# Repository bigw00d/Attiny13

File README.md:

# Attiny13 

This project is software and hardware resources to support my hobby. 

## Licence

   Licensed under the Apache License, Version 2.0 (the "License");
   you may not use this file except in compliance with the License.
   You may obtain a copy of the License at

       http://www.apache.org/licenses/LICENSE-2.0

   Unless required by applicable law or agreed to in writing, software
   distributed under the License is distributed on an "AS IS" BASIS,
   WITHOUT WARRANTIES OR CONDITIONS OF ANY KIND, either express or implied.
   See the License for the specific language governing permissions and
   limitations under the License.

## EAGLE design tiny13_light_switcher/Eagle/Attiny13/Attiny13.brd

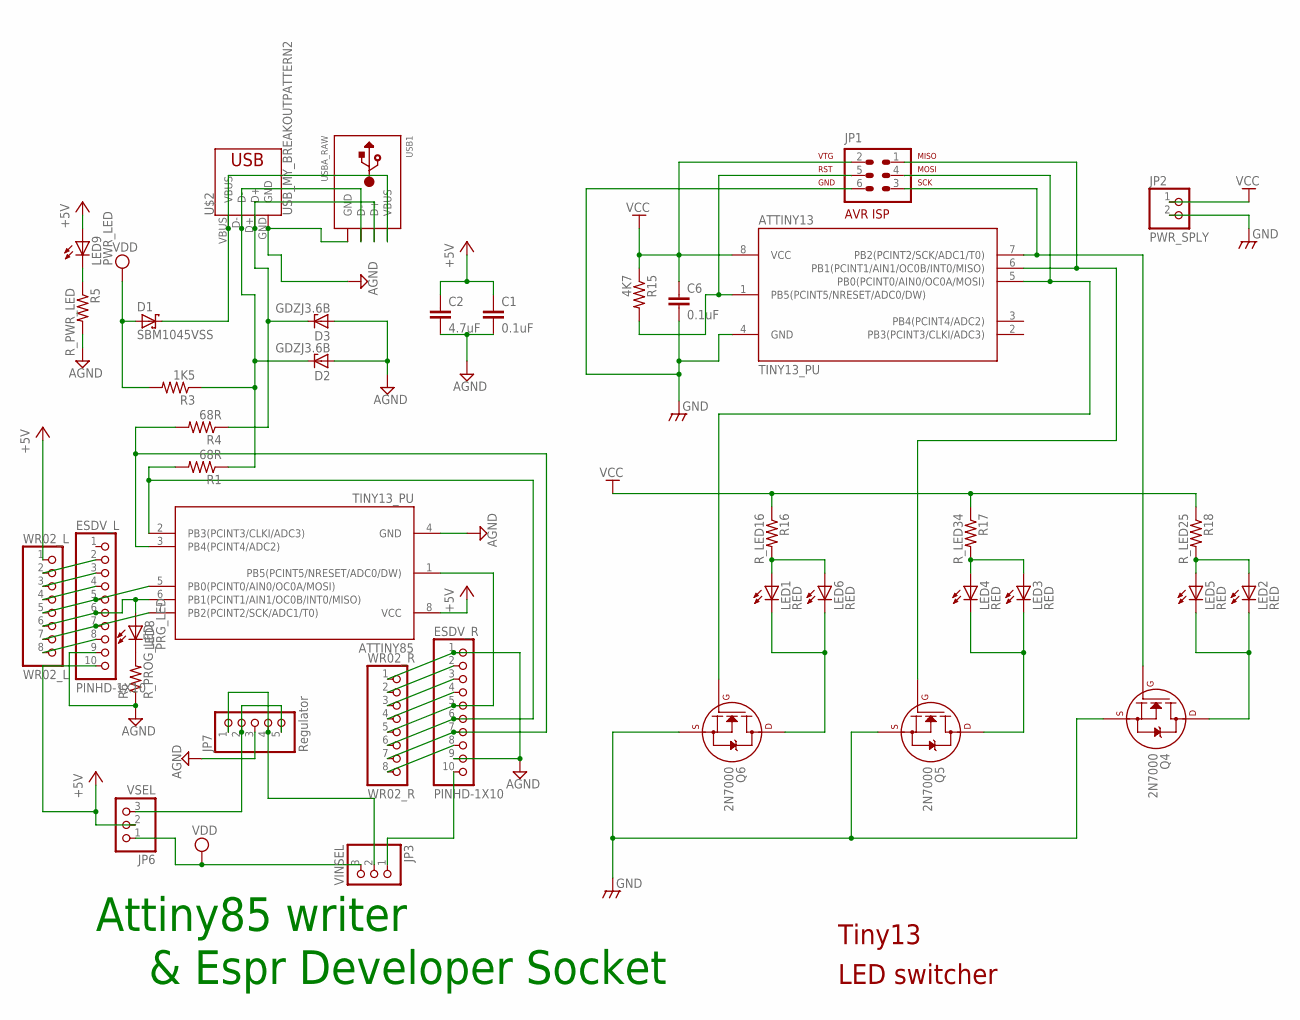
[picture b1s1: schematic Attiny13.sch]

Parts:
ATTINY13, ATTINY85: TINY13_PU; TINY_DIL08
C1, C6: 0.1uF; C050-025X075
C2: 4.7uF; C050-025X075
D1: SBM1045VSS; DO41-10
D2, D3: GDZJ3.6B; DO34Z7
ESDV_L: PINHD-1X10; 1X10-BIG
ESDV_R: PINHD-1X10; 1X10-BIG
JP1: AVR-ISP-6
JP2: PWR_SPLY; 1X02
JP3: VINSEL; 1X03
JP6: VSEL; 1X03
JP7: Regulator; 1X05
LED1, LED2, LED3, LED4, LED5, LED6: RED; SFH480
LED8: PRG_LED; SFH480
LED9: PWR_LED; SFH480
Q4, Q5, Q6: 2N7000; TO-92
R1, R4: 68R; 0204/7
R3: 1K5; 0204/7
R5: R_PWR_LED; 0204/7
R6: R_PROG_LED; 0204/7
R15: 4K7; 0204/7
R16: R_LED16; 0204/7
R17: R_LED34; 0204/7
R18: R_LED25; 0204/7
U$2: USB_MY_BREAKOUTPATTERN2; USB_MY_BREAKOUT2
USB1: USBA_RAW
WR02_L: WR02_L; 1X08-BIG
WR02_R: WR02_R; 1X08-BIG

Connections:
+5V: ATTINY85.8 (VCC), C1.1, C2.1, ESDV_L.10, JP6.2, LED9.A, WR02_L.1
AGND: ATTINY85.4 (GND), C1.2, C2.2, D2.A, D3.A, ESDV_L.9, ESDV_R.1, ESDV_R.9, JP7.3, R5.2, R6.1, U$2.GND, USB1.GND, WR02_R.1
GND: ATTINY13.4 (GND), C6.2, JP1.6, JP2.2, Q4.1 (S), Q5.1 (S), Q6.1 (S)
unnamed: D1.C, U$2.VBUS, USB1.VBUS
unnamed: ATTINY13.7 (PB2(PCINT2/SCK/ADC1/T0)), JP1.3, Q4.2 (G)
unnamed: ATTINY85.2 (PB3(PCINT3/CLKI/ADC3)), ESDV_R.6, R1.2, WR02_R.6
unnamed: D2.C, R1.1, R3.1, U$2.D-, USB1.D-
unnamed: LED1.K (C), LED6.K (C), Q6.3 (D)
unnamed: ATTINY13.5 (PB0(PCINT0/AIN0/OC0A/MOSI)), JP1.4, Q6.2 (G)
unnamed: ATTINY13.1 (PB5(PCINT5/NRESET/ADC0/DW)), JP1.5, R15.2
unnamed: ATTINY13.6 (PB1(PCINT1/AIN1/OC0B/INT0/MISO)), JP1.1, Q5.2 (G)
unnamed: LED2.K (C), LED5.K (C), Q4.3 (D)
unnamed: LED3.K (C), LED4.K (C), Q5.3 (D)
unnamed: ATTINY85.3 (PB4(PCINT4/ADC2)), ESDV_R.7, R4.2, WR02_R.7
unnamed: ATTINY85.1 (PB5(PCINT5/NRESET/ADC0/DW)), ESDV_R.5, WR02_R.5
unnamed: LED9.K (C), R5.1
unnamed: LED8.K (C), R6.2
unnamed: ATTINY85.6 (PB1(PCINT1/AIN1/OC0B/INT0/MISO)), ESDV_L.6, LED8.A, WR02_L.6
unnamed: ATTINY85.5 (PB0(PCINT0/AIN0/OC0A/MOSI)), ESDV_L.5, WR02_L.5
unnamed: JP3.2, JP7.1, JP7.4
unnamed: ATTINY85.7 (PB2(PCINT2/SCK/ADC1/T0)), ESDV_L.7, WR02_L.7
unnamed: D3.C, R4.1, U$2.D+, USB1.D+
unnamed: ESDV_R.10, JP3.1
unnamed: ESDV_L.2, WR02_L.2
unnamed: ESDV_L.3, WR02_L.3
unnamed: ESDV_L.4, WR02_L.4
unnamed: ESDV_L.8, WR02_L.8
unnamed: ESDV_R.2, WR02_R.2
unnamed: JP6.3, JP7.2, JP7.5
unnamed: ESDV_R.3, WR02_R.3
unnamed: ESDV_R.4, WR02_R.4
unnamed: ESDV_R.8, WR02_R.8
unnamed: LED1.A, LED6.A, R16.2
unnamed: LED3.A, LED4.A, R17.2
unnamed: LED2.A, LED5.A, R18.2
VCC: ATTINY13.8 (VCC), C6.1, JP1.2, JP2.1, R15.1, R16.1, R17.1, R18.1
VDD: D1.A, JP3.3, JP6.1, R3.2

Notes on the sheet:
Tiny13
LED switcher
Attiny85 writer
& Espr Developer Socket

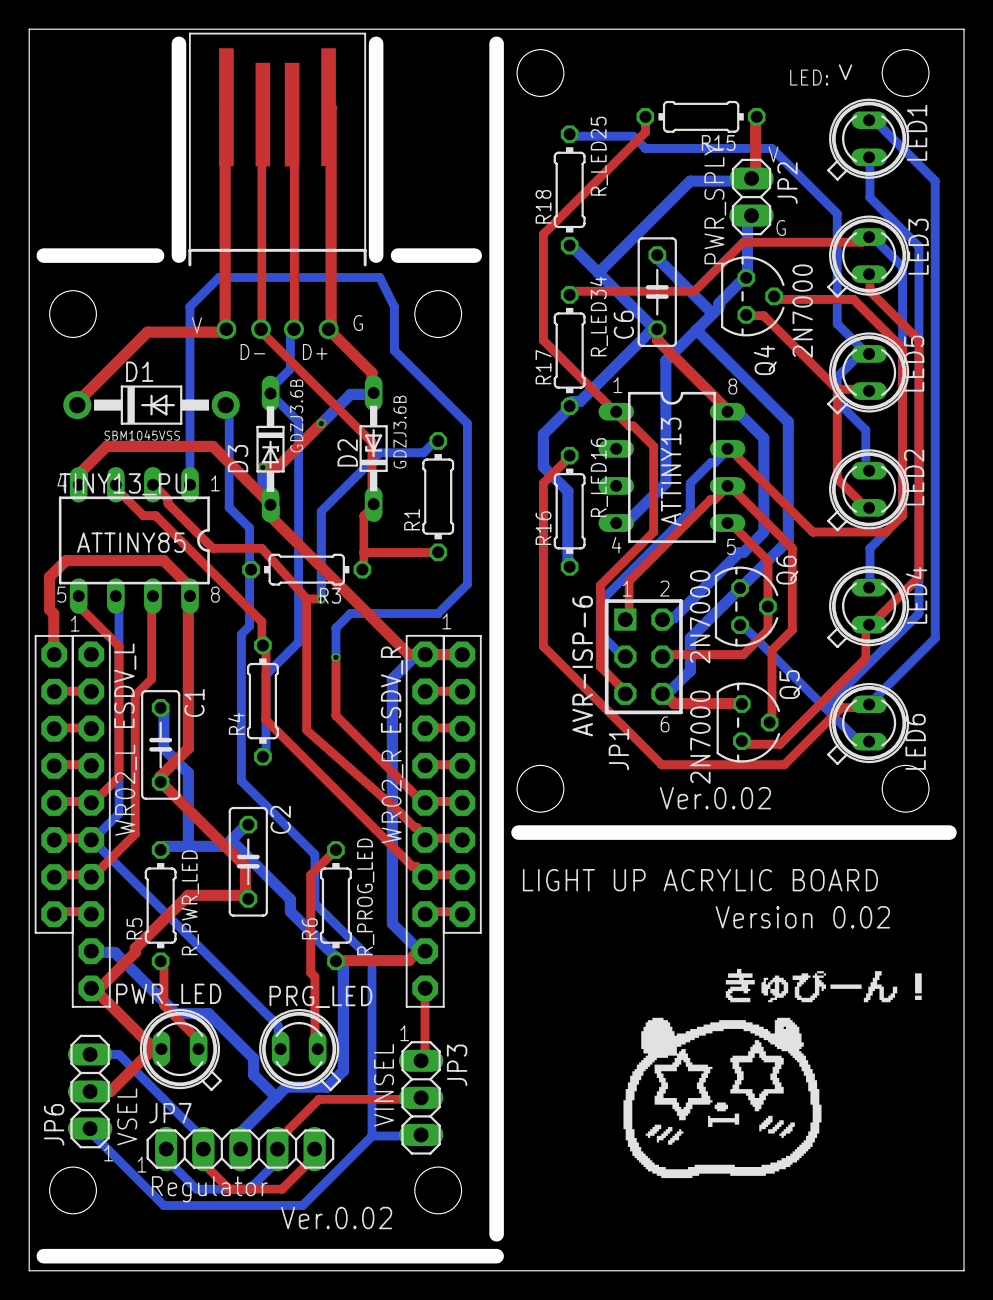
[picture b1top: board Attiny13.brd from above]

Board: 2 copper layers, 63.0 x 84.0 mm, 39 parts (0 on the bottom side), 37 nets.

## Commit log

2018-05-17 Add Jinkan light control source code.
2018-05-22 1st commit
2018-05-22 Remove no use parts.
2018-05-22 Remove wrong file.
2018-05-22 Add README file.
2018-05-22 Add temporary image.
2018-05-22 Change README.
2018-05-23 Add tiny85 writer.
2018-05-23 Change sub pin header to wroom02 breakout board.
2018-05-23 Add pattern diagram.
2018-05-23 Change USB connector.
2018-05-24 Add pattern.
2018-05-25 Fix USB & parts layout.
2018-05-25 Change capacitor package.
2018-05-25 Resolve DRC & ERC.
2018-05-25 Auto Routing OK.
2018-05-25 Fix Wiring.
2018-05-27 Add ground solid pattern.
2018-05-27 Add Synbol names.
2018-05-27 Change PCB Size.
2018-05-28 Fix Schematic File.
2018-06-04 Fix LED Direction & USB SMD Length.
2018-06-05 Spread Pin holes & Change LED Direction.
2018-06-11 Add Illustrator file for laser cutter 'HAJIME'.
2018-06-17 Add Arduino Src File(for light swither)
2018-07-06 Add Switch Control Function.
2018-08-16 add test file.
2018-08-16 add test file2
2018-08-22 Add test file
